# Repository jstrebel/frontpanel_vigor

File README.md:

# vigor frontpanel mit Folientastatur.

Bedienung:  Entwurf der das Bedieninterface der Kotrollerbox erklärt

Schemas:

Testcode:     Beispiel lesen der Tastatur input mit dem Arduino

TFT display:  Für die Anzeigen wird ein gut Dokumentierte Library verwendet.
Doku auf: https://github.com/gavinlyonsrepo/Display_Lib_RPI

Das ist der Code welcher der Entwickler für mich machte.
Dieser Code ist mit dem Raspi 4 getestet.
https://github.com/gavinlyonsrepo/ST7789_TFT_RPI/releases

Gavin hat die Beschreibung upgedatet, Grund war, dass der code den wir verwenden eine andere Library verwendet.
https://github.com/gavinlyonsrepo/ST7789_TFT_RPI

<<<<<<< Updated upstream
<<<<<<< Updated upstream
BEM: werde dieses Repository weiter organisieren und aufräumen 

## Installationen im Raspi

### bcm2835
```
curl -sL http://www.airspayce.com/mikem/bcm2835/bcm2835-1.75.tar.gz | tar xz
./configure
make
sudo make check
sudo make install
```

### redis 
https://fleetstack.io/blog/redis-on-raspberry-pi-setup
```
sudo apt install redis-server -y
```

Falls wenig RAM Memorybegrenzung:
```
sudo nano /etc/redis/redis.conf
maxmemory 100mb maxmemory-policy allkeys-lru
```

Hinzufügen zum Autostart und starten von redis 
```
sudo systemctl  enable  redis-server
sudo systemctl start redis-server
```

Testen:
```
redis-cli
set  testkey  "hello"
get testkey
```

### hiredis
```
sudo apt-get install libhiredis-dev
```
=======
BEM: Werde dieses Repository weiter organisieren und aufräumen
>>>>>>> Stashed changes
=======
BEM: Werde dieses Repository weiter organisieren und aufräumen
>>>>>>> Stashed changes

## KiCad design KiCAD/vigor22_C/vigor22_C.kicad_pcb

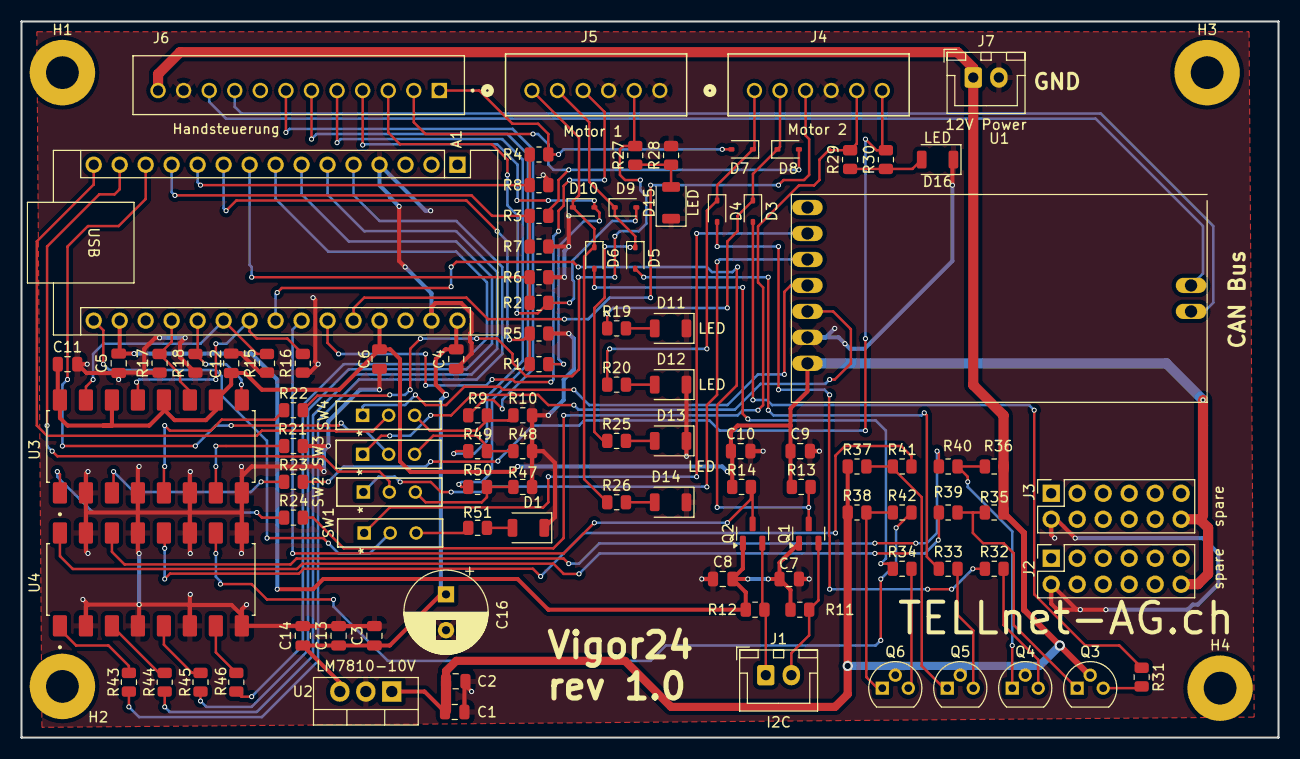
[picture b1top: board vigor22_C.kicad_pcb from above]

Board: 2 copper layers, 122.9 x 70.0 mm, 107 parts (0 on the bottom side), 82 nets.

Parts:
A1: Arduino_Nano_v3.x; Arduino_Nano
C1, C2, C3, C4, C5, C6, C7, C8, C9, C10, C11, C12, C13, C14: 47nF; C_0805_2012Metric
C16: 2.2uF; CP_Radial_D8.0mm_P3.50mm
D1, D11, D12, D13, D14, D15, D16: LED; LED_1206_3216Metric_ReverseMount_Hole1.8x2.4mm
D3, D4, D5, D6, D7, D8, D9, D10: D; D_SOD-323
H1, H2, H3, H4: MountingHole; MountingHole_3.2mm_M3_Pad
J1: I2C; JST_XH_B2B-XH-A_1x02_P2.50mm_Vertical
J2, J3: spare; PinSocket_2x06_P2.54mm_Vertical
J4: Motor 2; CONN_B6B-XH-JST
J5: Motor 1; CONN_B6B-XH-JST
J6: Handsteuerung; CONN_B12B-XH-JST
J7: 12V Power; JST_XH_B2B-XH-A_1x02_P2.50mm_Vertical
Q1, Q2: BSS138; SOT-23
Q3, Q4, Q5, Q6: Q_PNP_BEC; TO-92
R1, R2, R3, R4, R9, R49, R50: 1.2k; R_0805_2012Metric
R5, R6, R7, R8, R10, R39, R40, R41, R42, R47, R48, R51: 560; R_0805_2012Metric
R11, R12, R13, R14: 10k; R_0805_2012Metric
R15, R16, R17, R18, R31, R32, R33, R34, R35, R36, R37, R38: 470; R_0805_2012Metric
R19, R20, R25, R26, R27, R28, R29, R30: 2.2k; R_0805_2012Metric
R21, R22, R23, R24, R43, R44, R45, R46: 1k; R_0805_2012Metric
SW1, SW2, SW3, SW4: SW_Push_SPDT; wuert_WS-SLTV
U1: MCP2515
U2: LM7810-10V; TO-220-3_Vertical
U3, U4: LTV-847; SOIC254P1016X460-16N

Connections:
+3.3V: A1.17 (3V3), C5.2, C7.2, C8.2, Q1.1 (G), Q2.1 (G), R11.1, R12.1
+5V: A1.27 (+5V), C6.1, C9.1, C10.1, C11.1, C12.1, J2.12, J3.12, R13.1, R14.1, U1.7 (+5V), U3.10, U3.12, U3.14, U3.16
+10V: A1.30 (VIN), C3.1, C4.2, C13.1, C14.1, C16.1, U2.3 (VO)
+12V: C1.2, C2.2, J6.12, J7.1, Q3.2 (E), Q4.2 (E), Q5.2 (E), Q6.2 (E), R35.1, R36.1, R37.1, R38.1, U2.1 (VI)
CAN_H: J6.9, U1.9 (CAN_H)
CAN_L: J6.10, U1.8 (CAN_H)
D0: J6.7, R9.1
D6: J6.6, R50.1
D7: J6.5, R49.1
GND: A1.4 (GND), A1.29 (GND), C1.1, C2.1, C3.2, C4.1, C5.1, C6.2, C7.1, C8.1, C9.2, C10.2, C11.2, C12.2, C13.2, C14.2, C16.2, D1.1 (K), D11.1 (K), D12.1 (K), D13.1 (K), D14.1 (K), D15.1 (K), D16.1 (K), J2.2, J3.2, J4.4, J5.4, J5.6, J6.11, J7.2, R5.2, R6.2, R7.2, R8.2, R10.2, R15.1, R16.1, R17.1, R18.1, R21.2, R28.2, R47.2, R48.2, U1.6 (GND), U2.2 (GND), U3.2, U3.4, U3.6, U3.8, U4.2, U4.4, U4.6, U4.8, U4.9, U4.11, U4.13, U4.15
I2C SCL: J1.1, Q2.2 (S), R12.2
I2C SDA: J1.2, Q1.2 (S), R11.2
LH12-li ausfahren: D3.1 (K), D8.1 (K), J4.2, R19.1
LH12-li einfahren: D4.1 (K), D7.1 (K), J4.1, R20.1
LH12-re ausfahren: D5.1 (K), D9.1 (K), J5.2, R25.1
LH12-re einfahren: D6.1 (K), D10.1 (K), J5.1, R26.1
LI_auf_LH12: D3.2 (A), R31.1
LI_auf_sig: A1.5 (D2), R43.2
LI_zu_LH12: D4.2 (A), R32.1
LI_zu_sig: A1.6 (D3), R44.2
unnamed: A1.19 (A0), R17.2, U3.11
unnamed: A1.20 (A1), R18.2, U3.9
unnamed: A1.21 (A2), R15.2, U3.15
unnamed: A1.22 (A3), R16.2, U3.13
unnamed: A1.23 (A4), Q1.3 (D), R13.2
unnamed: A1.24 (A5), Q2.3 (D), R14.2
unnamed: A1.9 (D6), R2.2, R6.1
unnamed: A1.10 (D7), R1.2, R5.1
unnamed: A1.11 (D8), R4.2, R8.1
unnamed: A1.12 (D9), R3.2, R7.1
unnamed: A1.13 (D10), SW3.2 (B)
unnamed: A1.14 (D11), SW2.2 (B)
unnamed: A1.15 (D12), SW4.2 (B)
unnamed: A1.16 (D13), SW1.2 (B)
unnamed: D1.2 (A), R51.2
unnamed: D11.2 (A), R19.2
unnamed: D12.2 (A), R20.2
unnamed: D13.2 (A), R25.2
unnamed: D14.2 (A), R26.2
unnamed: D15.2 (A), R27.1, R28.1
unnamed: D16.2 (A), R29.1, R30.1
unnamed: J4.5, R24.2, R29.2
unnamed: J4.6, R23.2, R30.2
unnamed: J5.5, R22.2, R27.2
unnamed: Q3.1 (B), R35.2, R39.1
unnamed: Q3.3 (C), R31.2
unnamed: Q4.1 (B), R36.2, R40.1
unnamed: Q4.3 (C), R32.2
unnamed: Q5.1 (B), R37.2, R41.1
unnamed: Q5.3 (C), R33.2
unnamed: Q6.1 (B), R38.2, R42.1
unnamed: Q6.3 (C), R34.2
unnamed: R21.1, U3.7
unnamed: R22.1, U3.5
unnamed: R23.1, U3.3
unnamed: R24.1, U3.1
unnamed: R39.2, U4.16
unnamed: R40.2, U4.14
unnamed: R41.2, U4.12
unnamed: R42.2, U4.10
unnamed: R43.1, U4.1
unnamed: R44.1, U4.3
unnamed: R45.1, U4.5
unnamed: R46.1, U4.7
unnamed: SW1.1 (A), U1.2 (sck)
unnamed: R51.1, SW1.3 (C)
unnamed: SW2.1 (A), U1.3 (MOSI)
unnamed: R47.1, R50.2, SW2.3 (C)
unnamed: SW3.1 (A), U1.5 (CS)
unnamed: R48.1, R49.2, SW3.3 (C)
unnamed: SW4.1 (A), U1.4 (MISO)
unnamed: R9.2, R10.1, SW4.3 (C)
RE_auf_LH12: D5.2 (A), R33.1
RE_auf_sig: A1.7 (D4), R45.2
RE_zu_LH12: D6.2 (A), R34.1
RE_zu_sig: A1.8 (D5), R46.2
li-Position poti H: A1.26 (A7), J4.3
li-manuell-oeffnen: D8.2 (A), J6.2, R3.1
li-manuell-schliessen: D7.2 (A), J6.1, R4.1
re-Position poti H: A1.25 (A6), J5.3
re-manuell-oeffnen: D10.2 (A), J6.4, R1.1
re-manuell-schliessen: D9.2 (A), J6.3, R2.1

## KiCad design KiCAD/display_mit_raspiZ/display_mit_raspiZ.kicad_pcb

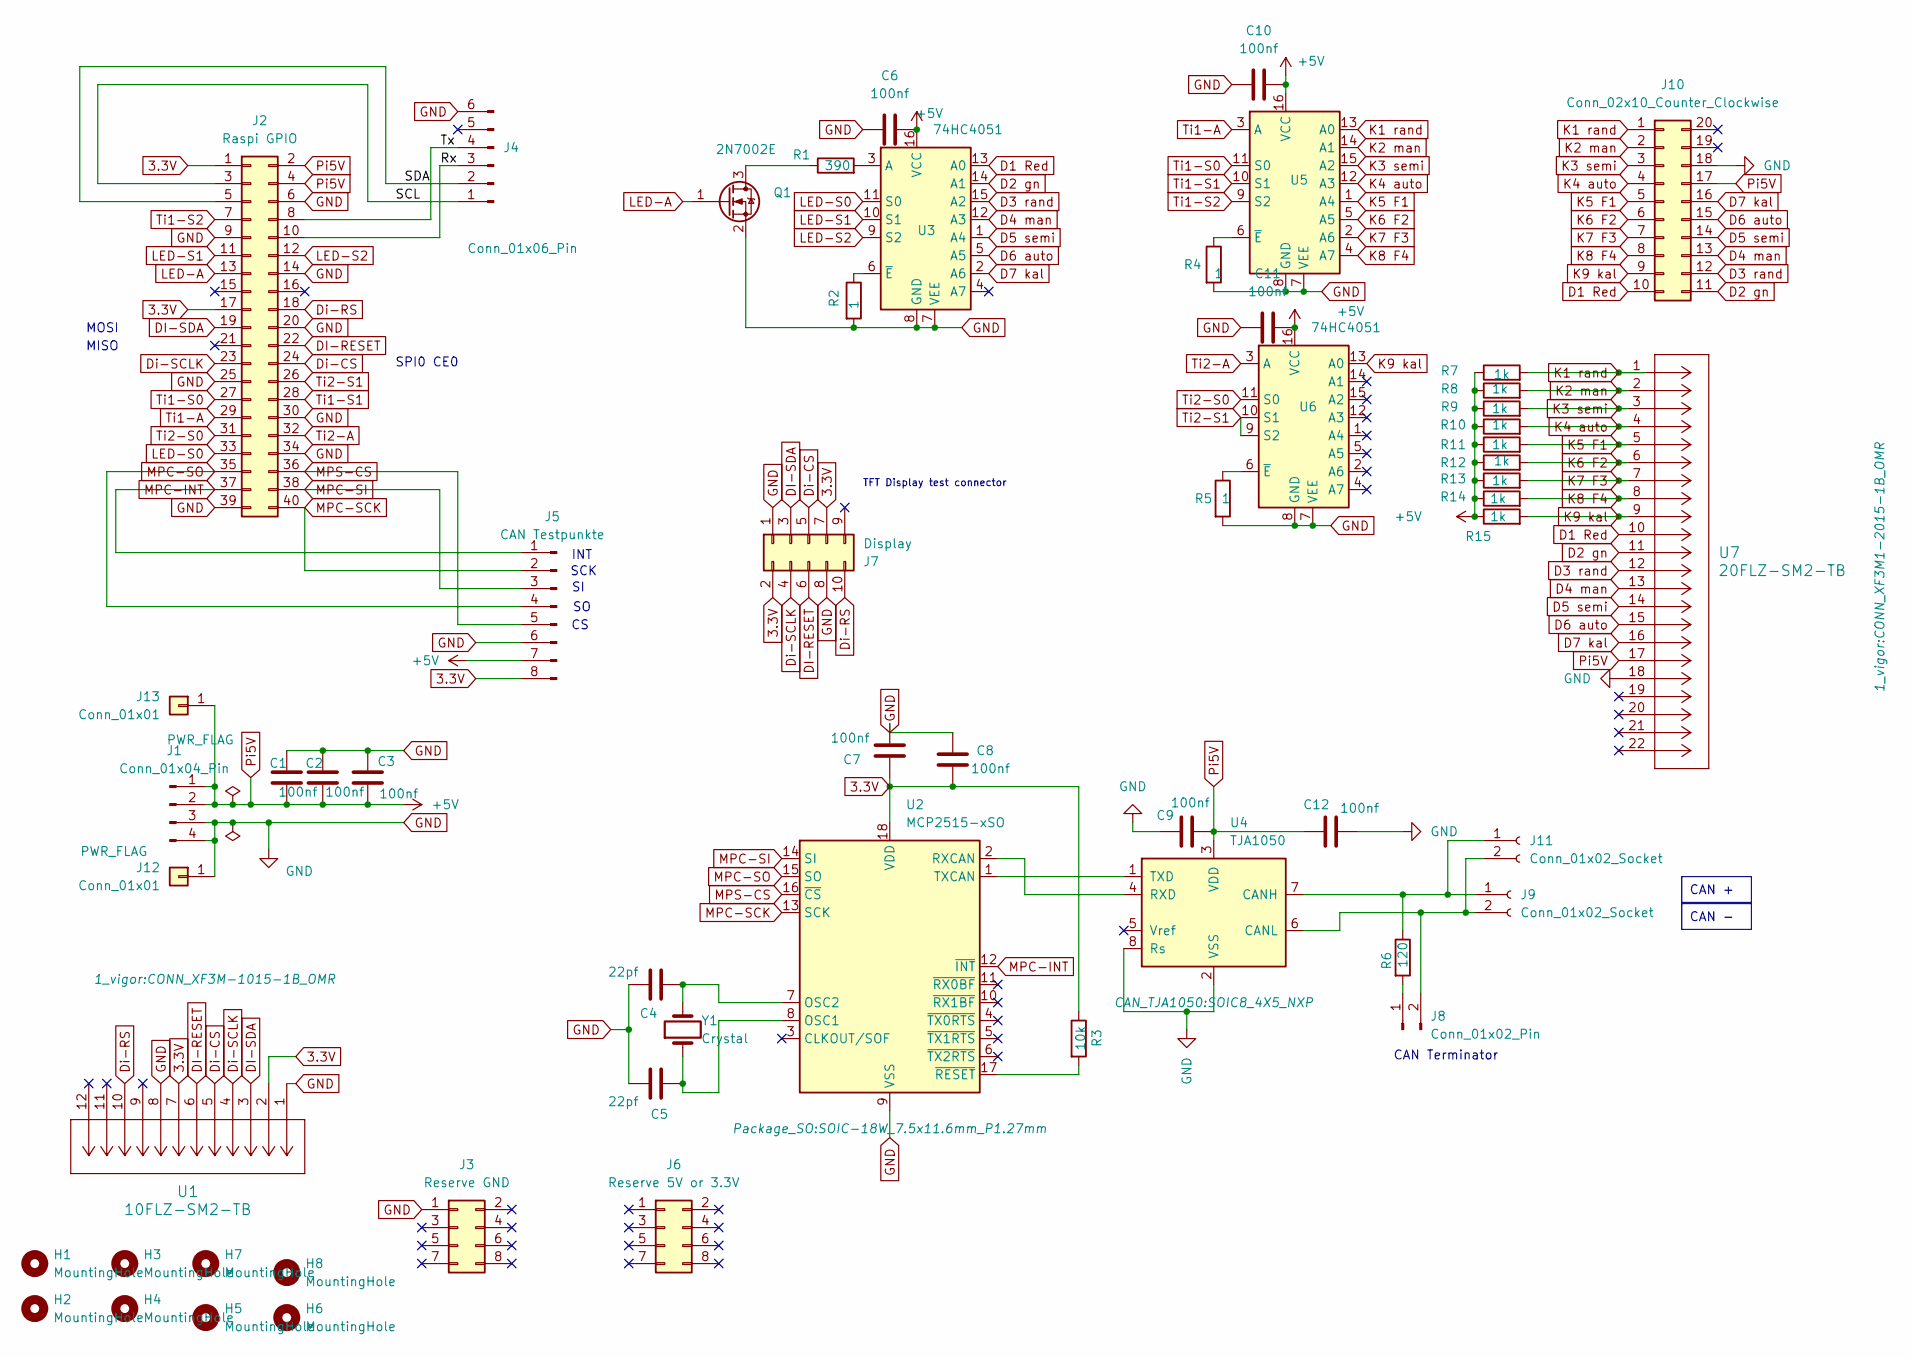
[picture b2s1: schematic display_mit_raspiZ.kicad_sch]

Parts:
C1, C2, C3, C6, C7, C8, C9, C10, C11, C12: 100nf; C_0805_2012Metric
C4, C5: 22pf; CAPC17595_87N_KEM
H1, H2, H3, H4, H5, H6, H7, H8: MountingHole; MountingHole_3.2mm_M3_ISO7380_Pad
J1: Conn_01x04_Pin; PinHeader_1x04_P2.54mm_Vertical
J2: Raspi GPIO; PinHeader_2x20_P2.54mm_Vertical
J3: Reserve GND; PinHeader_2x05_P2.54mm_Vertical
J4: Conn_01x06_Pin; PinHeader_1x06_P2.54mm_Vertical
J5: CAN Testpunkte; PinHeader_1x08_P2.54mm_Vertical
J6: Reserve 5V or 3.3V; PinHeader_2x05_P2.54mm_Vertical
J7: Display; PinHeader_2x05_P2.54mm_Vertical
J8: Conn_01x02_Pin; PinHeader_1x02_P2.54mm_Vertical
J9, J11: Conn_01x02_Socket; PinHeader_1x02_P2.54mm_Vertical
J10: Conn_02x10_Counter_Clockwise; PinHeader_2x10_P2.54mm_Vertical
J12, J13: Conn_01x01; Flachst_2.5mm
Q1: 2N7002E; SOT-23
R1: 390; R_1206_3216Metric
R2, R4, R5: 1; R_0805_2012Metric
R3: 10k; R_0805_2012Metric
R6: 120; R_1206_3216Metric
R7, R8, R9, R10, R11, R12, R13, R14, R15: 1k; R_0805_2012Metric
U1: 10FLZ-SM2-TB; CONN_XF3M-1015-1B_OMR
U2: MCP2515-xSO; SOIC-18W_7.5x11.6mm_P1.27mm
U3, U5, U6: 74HC4051; SOIC-16_3.9x9.9mm_P1.27mm
U4: TJA1050; SOIC8_4X5_NXP
U7: 20FLZ-SM2-TB; CONN_XF3M1-2015-1B_OMR
Y1: Crystal; Crystal_SMD_Abracon_ABM3-2Pin_5.0x3.2mm_HandSoldering

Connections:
3.3V: C7.2, C8.2, J2.1, J2.17, J5.8, J7.2, J7.7, R3.1, U1.2, U1.7, U2.18 (VDD)
/Rx: J2.10, J4.3
/SCL: J2.3, J4.1
/SDA: J2.5, J4.2
/Tx: J2.8, J4.4
D1 Red: J10.10, U3.13 (A0), U7.10
D2 gn: J10.11, U3.14 (A1), U7.11
D3 rand: J10.12, U3.15 (A2), U7.12
D4 man: J10.13, U3.12 (A3), U7.13
D5 semi: J10.14, U3.1 (A4), U7.14
D6 auto: J10.15, U3.5 (A5), U7.15
D7 kal: J10.16, U3.2 (A6), U7.16
DI-RESET: J2.22, J7.6, U1.6
DI-SDA: J2.19, J7.3, U1.3
Di-CS: J2.24, J7.5, U1.5
Di-RS: J2.18, J7.10, U1.10
Di-SCLK: J2.23, J7.4, U1.4
GND: C1.1, C2.1, C3.1, C4.1, C5.1, C6.1, C7.1, C8.1, C9.1, C10.1, C11.1, C12.2, J1.3, J1.4, J2.6, J2.9, J2.14, J2.20, J2.25, J2.30, J2.34, J2.39, J3.1, J4.6, J5.6, J7.1, J7.8, J10.18, J12.1, Q1.2 (S), R2.2, R4.2, R5.2, U1.1, U1.8, U2.9 (VSS), U3.7 (VEE), U3.8 (GND), U4.2 (VSS), U4.8 (Rs), U5.7 (VEE), U5.8 (GND), U6.7 (VEE), U6.8 (GND), U7.18
K1 rand: J10.1, R7.2, U5.13 (A0), U7.1
K2 man: J10.2, R8.2, U5.14 (A1), U7.2
K3 semi: J10.3, R9.2, U5.15 (A2), U7.3
K4 auto: J10.4, R10.2, U5.12 (A3), U7.4
K5 F1: J10.5, R11.2, U5.1 (A4), U7.5
K6 F2: J10.6, R12.2, U5.5 (A5), U7.6
K7 F3: J10.7, R13.2, U5.2 (A6), U7.7
K8 F4: J10.8, R14.2, U5.4 (A7), U7.8
K9 kal: J10.9, R15.2, U6.13 (A0), U7.9
LED-A: J2.13, Q1.1 (G)
LED-S0: J2.33, U3.11 (S0)
LED-S1: J2.11, U3.10 (S1)
LED-S2: J2.12, U3.9 (S2)
MPC-INT: J2.37, J5.1, U2.12 (~INT)
MPC-SCK: J2.40, J5.2, U2.13 (SCK)
MPC-SI: J2.38, J5.3, U2.14 (SI)
MPC-SO: J2.35, J5.4, U2.15 (SO)
MPS-CS: J2.36, J5.5, U2.16 (~CS)
unnamed: J8.1, R6.2
unnamed: J9.1, J11.1, R6.1, U4.7 (CANH)
unnamed: J8.2, J9.2, J11.2, U4.6 (CANL)
unnamed: Q1.3 (D), R1.1
unnamed: C5.2, U2.8 (OSC1), Y1.1
unnamed: C4.2, U2.7 (OSC2), Y1.2
unnamed: U2.2 (RXCAN), U4.4 (RXD)
unnamed: U2.1 (TXCAN), U4.1 (TXD)
unnamed: R3.2, U2.17 (~RESET)
unnamed: R1.2, U3.3 (A)
unnamed: R2.1, U3.6 (~E)
unnamed: R4.1, U5.6 (~E)
unnamed: R5.1, U6.6 (~E)
Pi5V: C1.2, C2.2, C3.2, C6.2, C9.2, C10.2, C11.2, C12.1, J1.1, J1.2, J2.2, J2.4, J5.7, J10.17, J13.1, R7.1, R8.1, R9.1, R10.1, R11.1, R12.1, R13.1, R14.1, R15.1, U3.16 (VCC), U4.3 (VDD), U5.16 (VCC), U6.16 (VCC), U7.17
Ti1-A: J2.29, U5.3 (A)
Ti1-S0: J2.27, U5.11 (S0)
Ti1-S1: J2.28, U5.10 (S1)
Ti1-S2: J2.7, U5.9 (S2)
Ti2-A: J2.32, U6.3 (A)
Ti2-S0: J2.31, U6.11 (S0)
Ti2-S1: J2.26, U6.9 (S2), U6.10 (S1)

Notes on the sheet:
CAN +
CAN -
SCK
CAN Terminator
MISO
SPI0 CE0
INT
MOSI
TFT Display test connector

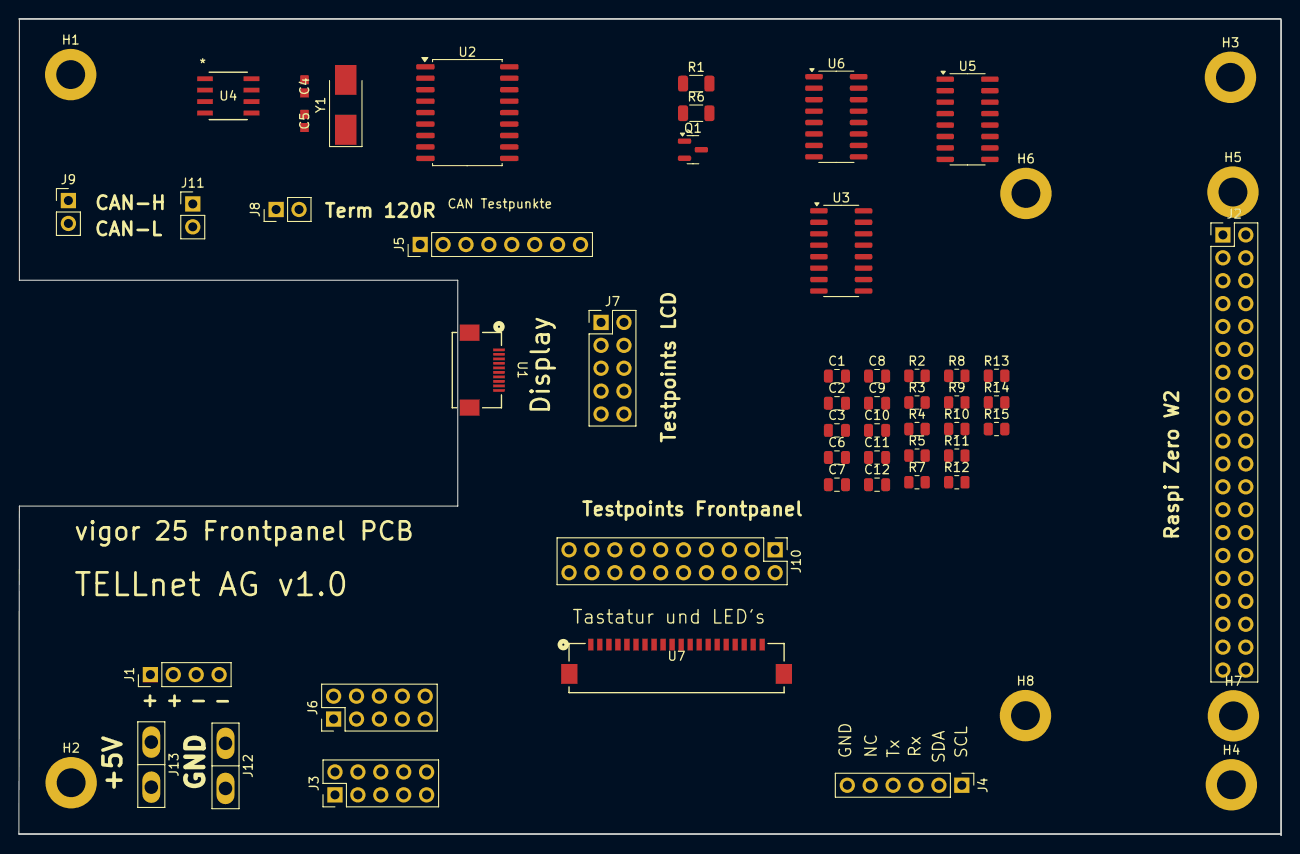
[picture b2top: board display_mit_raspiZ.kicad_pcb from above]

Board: 2 copper layers, 140.0 x 90.5 mm, 57 parts (0 on the bottom side), 57 nets.

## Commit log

2024-10-18 Create Design Specs
2024-10-22 Update Design Specs
2024-10-23 Raspi SPI Interface
2024-10-23 Add files via upload
    Prinzipschema Controller
2024-11-20 integrated basic can communication to transfer states
2025-02-11 Initial draft. Da muss noch Struktir rein
2025-02-11 Folder fuer test code
2025-02-11 Aktualisieren von display_angepasst_landscape_7789_raspi .rtf
    Rtf header entfernt
2025-02-12 updte Design Specs
2025-02-12 add schema ordner
2025-02-12 add schemas
2025-02-12 convertiert rtf -> txt
2025-02-13 diverse update und Ergänzungen
2025-02-13 div kleine updates
2025-02-13 file name geändert
2025-02-13 Create motor_regler.pdf
    zugefügt Schema Regler
2025-02-17 ergänzungen
2025-02-24 diverse updates
2025-03-04 Update README.md
    Referenz zum verwendeten Display Code
2025-03-04 Update Mailverkehr mit dem maintainer disply code.txt
    kosmetik
2025-03-04 Update Mailverkehr mit dem maintainer disply code.txt
    test aenderung ID
2025-03-12 Create display_lib_install_auf_neuem_Raspi.txt
    beschreibt die Installation auf einem neuen Raspi bei dem nur die lite version installiert ist
2025-03-13 Update README.md
    Verbesserte Erklärung zur verwendeten bcm2835 Library
2025-06-03 Skizze Randstreuen, Korrekturen PCB pendent
2025-06-06 KiCAD Files published
2025-06-06 Schema entfernt, Aktuelle Schema ist nun unter KiCAD
2025-06-23 Print in Controllerbox hinzugefügt
    Entkopplungskondensator bei MCP2515 Reset hinzugefügt
    MCP2515 Speisung auf 5V angepasst
    Kosmetik
2025-06-23 Ti2-S1 und -S2 am Raspi GPIO geändert
2025-06-23 added HMI_Design
2025-06-30 updated calib display
    changed "abdrehen" to "auf" und "zu"
